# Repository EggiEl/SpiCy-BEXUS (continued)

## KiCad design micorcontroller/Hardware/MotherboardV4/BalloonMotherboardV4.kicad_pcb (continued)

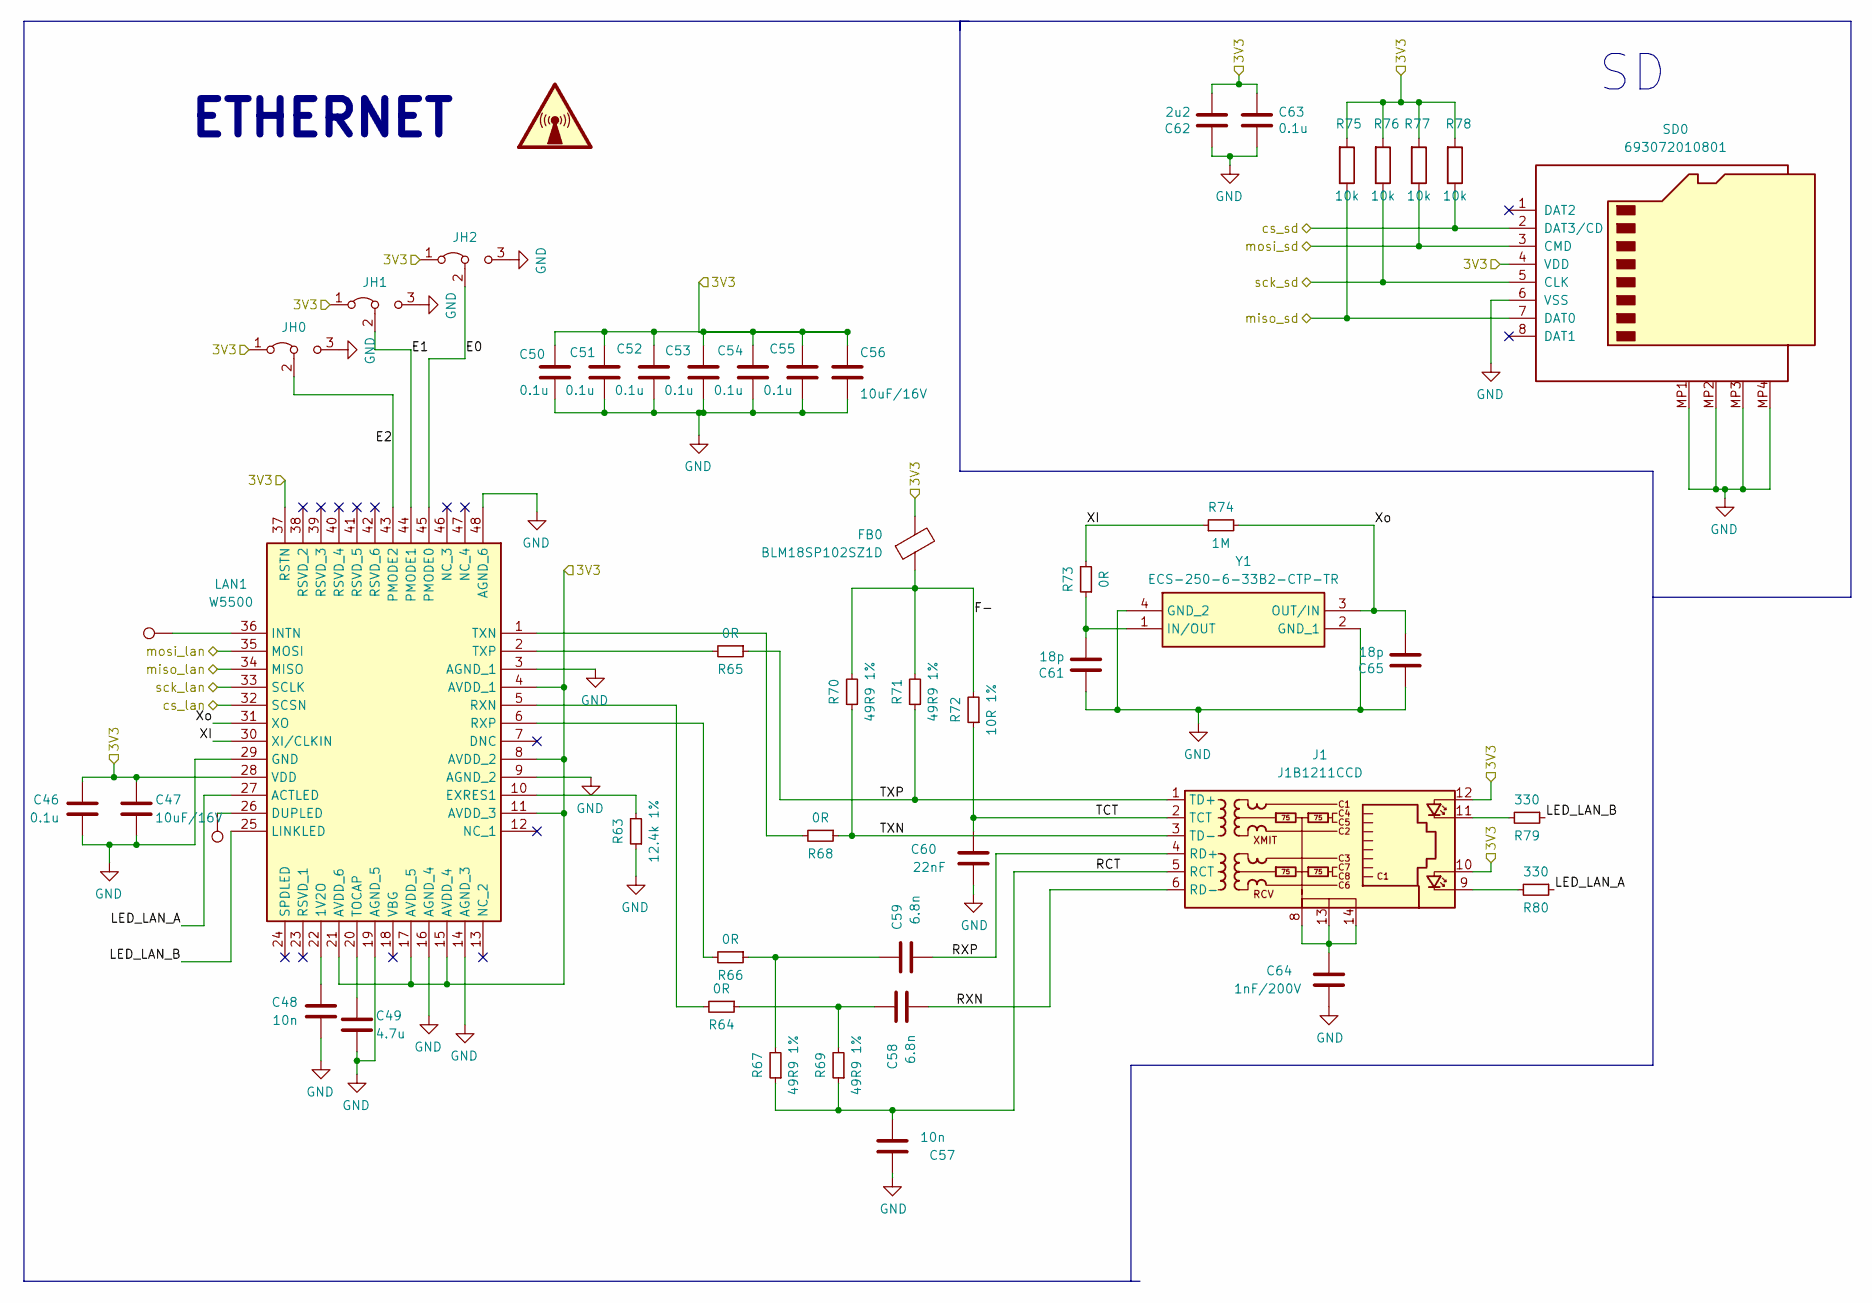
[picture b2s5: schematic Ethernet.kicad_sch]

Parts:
C46, C50, C51, C52, C53, C54, C55, C63: 0.1u; C_0402_1005Metric_Pad0.74x0.62mm_HandSolder
C47, C56: 10uF/16V; C_0805_2012Metric_Pad1.18x1.45mm_HandSolder
C48, C57: 10n; C_0805_2012Metric_Pad1.18x1.45mm_HandSolder
C49: 4.7u; C_0805_2012Metric_Pad1.18x1.45mm_HandSolder
C58, C59: 6.8n; C_0805_2012Metric_Pad1.18x1.45mm_HandSolder
C60: 22nF; C_0805_2012Metric_Pad1.18x1.45mm_HandSolder
C61, C65: 18p; C_0402_1005Metric_Pad0.74x0.62mm_HandSolder
C62: 2u2; C_0805_2012Metric_Pad1.18x1.45mm_HandSolder
C64: 1nF/200V; C_0805_2012Metric_Pad1.18x1.45mm_HandSolder
FB0: BLM18SP102SZ1D; BLM18SP221SN1B; Mouser Part Number 81-BLM18SP102SZ1D
J1: J1B1211CCD; Mouser Part Number 950-J1B1211CCD
JH0, JH1, JH2: Jumper_3_Bridged12; SolderJumper-3_P1.3mm_Bridged12_RoundedPad1.0x1.5mm_NumberL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
LAN1: W5500; QFP50P900X900X160-48N; Mouser Part Number 950-W5500
R63: 12.4k 1%; R_0603_1608Metric_Pad0.98x0.95mm_HandSolder
R64, R65, R66, R68, R73: 0R; R_0603_1608Metric_Pad0.98x0.95mm_HandSolder
R67, R69, R70, R71: 49R9 1%; R_0603_1608Metric_Pad0.98x0.95mm_HandSolder
R72: 10R 1%; R_0603_1608Metric_Pad0.98x0.95mm_HandSolder
R74: 1M; R_0603_1608Metric_Pad0.98x0.95mm_HandSolder
R75, R76, R77, R78: 10k; R_0603_1608Metric_Pad0.98x0.95mm_HandSolder
R79, R80: 330; R_0603_1608Metric_Pad0.98x0.95mm_HandSolder
SD0: 693072010801; Mouser Part Number 710-693072010801
TP3, TP4: TestPoint; TestPoint_Pad_D1.0mm
Y1: ECS-250-6-33B2-CTP-TR; ECS250633B2CTPTR; Mouser Part Number 520-250-6-33B2-CTPTR

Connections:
/3V3lan: C46.2, C47.2, C50.2, C51.2, C52.2, C53.2, C54.2, C55.2, C56.2, C62.2, C63.1, FB0.2, J1.10, J1.12, JH0.1 (A), JH1.1 (A), JH2.1 (A), LAN1.4 (AVDD_1), LAN1.8 (AVDD_2), LAN1.11 (AVDD_3), LAN1.15 (AVDD_4), LAN1.17 (AVDD_5), LAN1.21 (AVDD_6), LAN1.28 (VDD), LAN1.37 (RSTN), R75.2, R76.2, R77.2, R78.2, SD0.4 (VDD); also elsewhere on the board
/EthernetaSD/E0: JH2.2 (C), LAN1.45 (PMODE0)
/EthernetaSD/E1: JH1.2 (C), LAN1.44 (PMODE1)
/EthernetaSD/E2: JH0.2 (C), LAN1.43 (PMODE2)
/EthernetaSD/F-: FB0.1, R70.2, R71.2, R72.2
/EthernetaSD/LED_LAN_A: LAN1.27 (ACTLED), R80.1
/EthernetaSD/LED_LAN_B: LAN1.25 (LINKLED), R79.1
/EthernetaSD/RCT: C57.1, J1.5 (RCT), R67.1, R69.1
/EthernetaSD/RXN: C58.1, J1.6 (RD-)
/EthernetaSD/RXP: C59.1, J1.4 (RD+)
/EthernetaSD/TCT: C60.2, J1.2 (TCT), R72.1
/EthernetaSD/TXN: J1.3 (TD-), R68.1, R70.1
/EthernetaSD/TXP: J1.1 (TD+), R65.1, R71.1
/EthernetaSD/XI: LAN1.30 (XI/CLKIN), R73.2, R74.1
/EthernetaSD/Xo: C65.2, LAN1.31 (XO), R74.2, Y1.3 (OUT/IN)
/EthernetaSD/cs_lan: LAN1.32 (SCSN); also elsewhere on the board
/EthernetaSD/cs_sd: R78.1, SD0.2 (DAT3/CD); also elsewhere on the board
/EthernetaSD/miso_lan: LAN1.34 (MISO); also elsewhere on the board
/EthernetaSD/miso_sd: R75.1, SD0.7 (DAT0); also elsewhere on the board
/EthernetaSD/mosi_lan: LAN1.35 (MOSI); also elsewhere on the board
/EthernetaSD/mosi_sd: R77.1, SD0.3 (CMD); also elsewhere on the board
/EthernetaSD/sck_lan: LAN1.33 (SCLK); also elsewhere on the board
/EthernetaSD/sck_sd: R76.1, SD0.5 (CLK); also elsewhere on the board
GND: C46.1, C47.1, C48.1, C49.1, C50.1, C51.1, C52.1, C53.1, C54.1, C55.1, C56.1, C57.2, C60.1, C61.1, C62.1, C63.2, C64.1, C65.1, JH0.3 (B), JH1.3 (B), JH2.3 (B), LAN1.3 (AGND_1), LAN1.9 (AGND_2), LAN1.14 (AGND_3), LAN1.16 (AGND_4), LAN1.19 (AGND_5), LAN1.29 (GND), LAN1.48 (AGND_6), R63.1, SD0.6 (VSS), SD0.MP1, SD0.MP2, SD0.MP3, SD0.MP4, Y1.2 (GND_1), Y1.4 (GND_2); also elsewhere on the board
unnamed: C58.2, R64.1, R69.2
unnamed: C59.2, R66.1, R67.2
unnamed: C64.2, J1.8, J1.13, J1.14
unnamed: J1.9, R80.2
unnamed: J1.11, R79.2
unnamed: C48.2, LAN1.22 (1V2O)
unnamed: LAN1.26 (DUPLED), TP4.1
unnamed: LAN1.10 (EXRES1), R63.2
unnamed: LAN1.36 (INTN), TP3.1
unnamed: LAN1.5 (RXN), R64.2
unnamed: LAN1.6 (RXP), R66.2
unnamed: C49.2, LAN1.20 (TOCAP)
unnamed: LAN1.1 (TXN), R68.2
unnamed: LAN1.2 (TXP), R65.2
unnamed: C61.2, R73.1, Y1.1 (IN/OUT)

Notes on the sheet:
ETHERNET

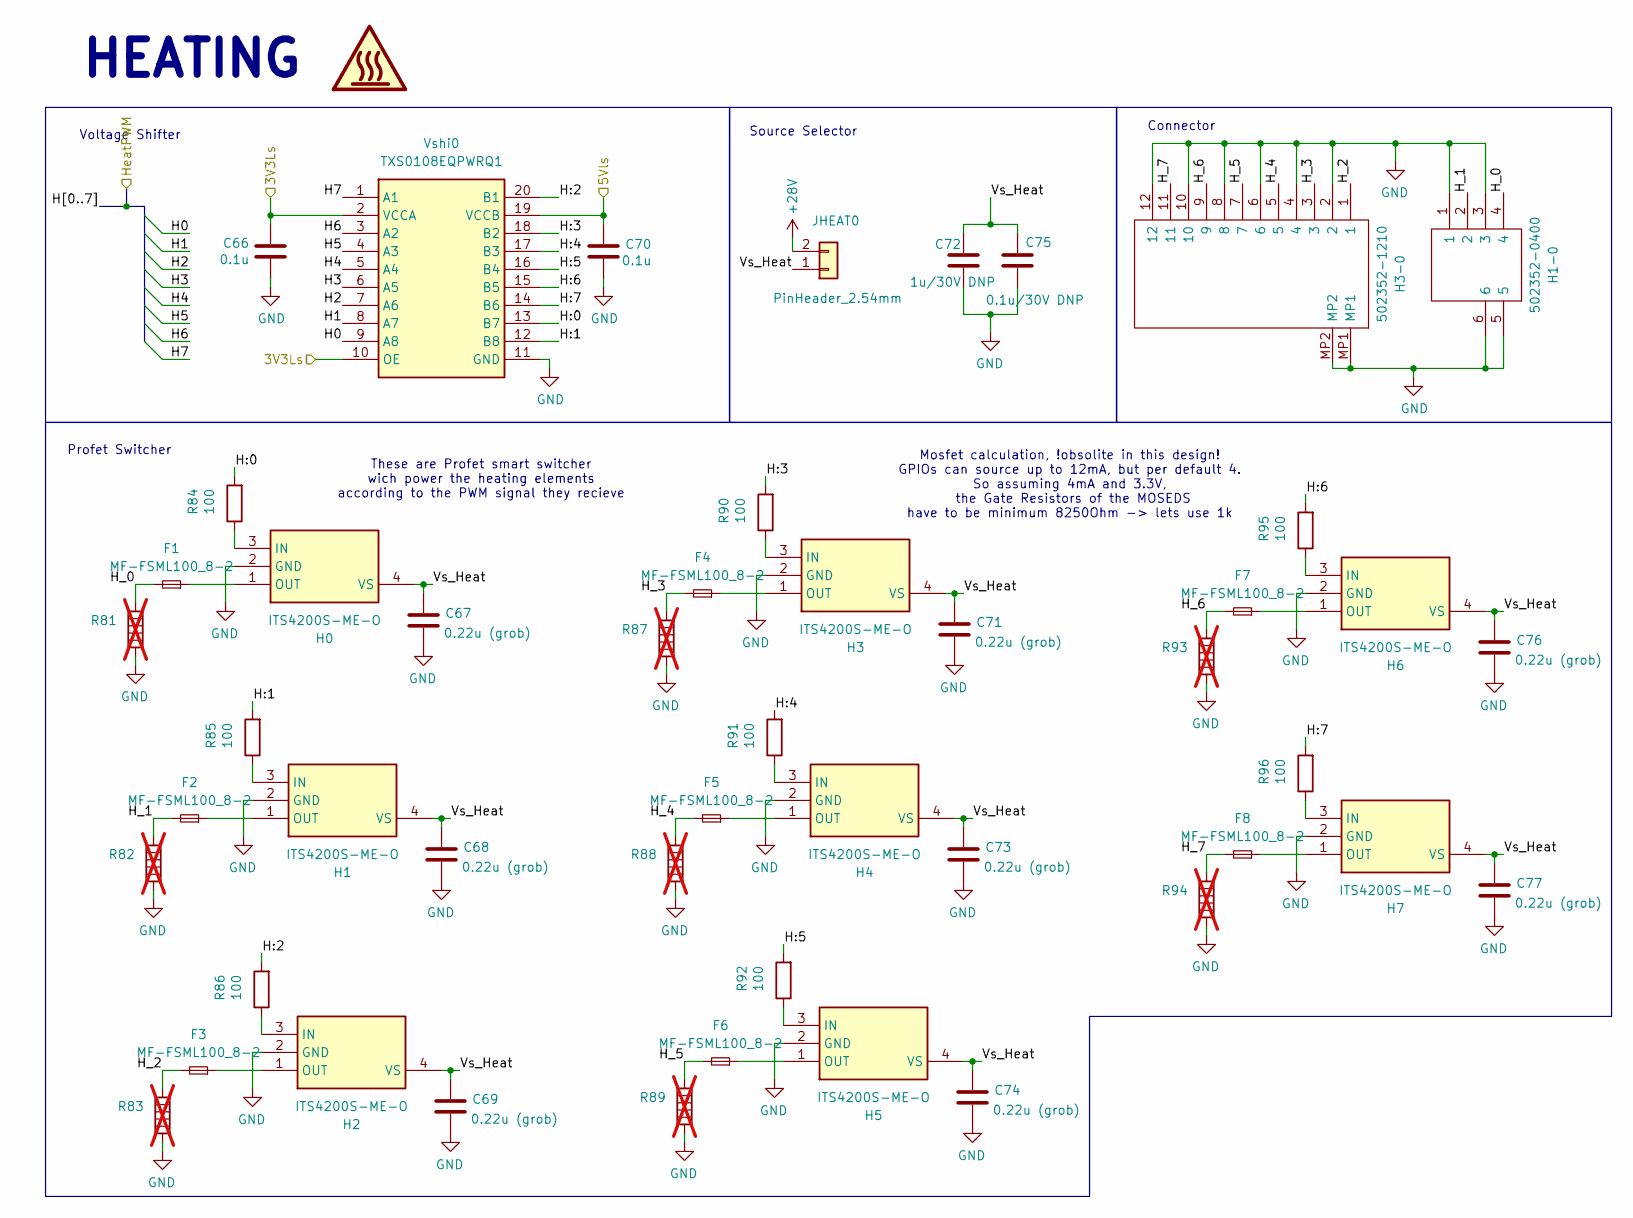
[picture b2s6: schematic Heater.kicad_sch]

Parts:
C66, C70: 0.1u; C_0402_1005Metric
C67, C68, C69, C71, C73, C74, C76, C77: 0.22u (grob); C_0402_1005Metric
C72: 1u/30V DNP; C_0805_2012Metric_Pad1.18x1.45mm_HandSolder
C75: 0.1u/30V DNP; C_0805_2012Metric_Pad1.18x1.45mm_HandSolder
F1, F2, F3, F4, F5, F6, F7, F8: MF-FSML100_8-2; FUSC1608X70N; Mouser Part Number 652-MF-FSML100/8-2
H0, H1, H2, H3, H4, H5, H6, H7: ITS4200S-ME-O; SOT230P700X170-4N; Mouser Part Number 726-ITS4200S-ME-O
H1-0: 502352-0400; 5023520400; Mouser Part Number 538-502352-0400
H3-0: 502352-1210; 5023521210; Mouser Part Number 538-502352-1210
JHEAT0: PinHeader_2.54mm; PinHeader_1x02_P2.54mm_Vertical
R81, R82, R83, R87, R88, R89, R93, R94: Heater; not fitted
R84, R85, R86, R90, R91, R92, R95, R96: 100; R_0603_1608Metric_Pad0.98x0.95mm_HandSolder
Vshi0: TXS0108EQPWRQ1; SOP65P640X120-20N; Mouser Part Number 595-TXS0108EQPWRQ1

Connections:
+28V: JHEAT0.2; also elsewhere on the board
/3V3_rest: C66.1, Vshi0.2 (VCCA), Vshi0.10 (OE); also elsewhere on the board
/5V: C70.1, Vshi0.19 (VCCB); also elsewhere on the board
/Heater/H0: Vshi0.9 (A8); also elsewhere on the board
/Heater/H1: Vshi0.8 (A7); also elsewhere on the board
/Heater/H2: Vshi0.7 (A6); also elsewhere on the board
/Heater/H3: Vshi0.6 (A5); also elsewhere on the board
/Heater/H4: Vshi0.5 (A4); also elsewhere on the board
/Heater/H5: Vshi0.4 (A3); also elsewhere on the board
/Heater/H6: Vshi0.3 (A2); also elsewhere on the board
/Heater/H7: Vshi0.1 (A1); also elsewhere on the board
/Heater/H:0: R84.2, Vshi0.13 (B7)
/Heater/H:1: R85.2, Vshi0.12 (B8)
/Heater/H:2: R86.2, Vshi0.20 (B1)
/Heater/H:3: R90.2, Vshi0.18 (B2)
/Heater/H:4: R91.2, Vshi0.17 (B3)
/Heater/H:5: R92.2, Vshi0.16 (B4)
/Heater/H:6: R95.2, Vshi0.15 (B5)
/Heater/H:7: R96.2, Vshi0.14 (B6)
/Heater/H_0: F1.2, H1-0.4, R81.1
/Heater/H_1: F2.2, H1-0.2, R82.1
/Heater/H_2: F3.2, H3-0.1, R83.1
/Heater/H_3: F4.2, H3-0.3, R87.1
/Heater/H_4: F5.2, H3-0.5, R88.1
/Heater/H_5: F6.2, H3-0.7, R89.1
/Heater/H_6: F7.2, H3-0.9, R93.1
/Heater/H_7: F8.2, H3-0.11, R94.1
/Heater/Vs_Heat: C67.1, C68.1, C69.1, C71.1, C72.2, C73.1, C74.1, C75.1, C76.1, C77.1, H0.4 (VS), H1.4 (VS), H2.4 (VS), H3.4 (VS), H4.4 (VS), H5.4 (VS), H6.4 (VS), H7.4 (VS), JHEAT0.1
GND: C66.2, C67.2, C68.2, C69.2, C70.2, C71.2, C72.1, C73.2, C74.2, C75.2, C76.2, C77.2, H0.2 (GND), H1.2 (GND), H1-0.1, H1-0.3, H1-0.5, H1-0.6, H2.2 (GND), H3.2 (GND), H3-0.2, H3-0.4, H3-0.6, H3-0.8, H3-0.10, H3-0.12, H3-0.MP1, H3-0.MP2, H4.2 (GND), H5.2 (GND), H6.2 (GND), H7.2 (GND), R81.2, R82.2, R83.2, R87.2, R88.2, R89.2, R93.2, R94.2, Vshi0.11 (GND); also elsewhere on the board
unnamed: H0.3 (IN), R84.1
unnamed: F1.1, H0.1 (OUT)
unnamed: H1.3 (IN), R85.1
unnamed: F2.1, H1.1 (OUT)
unnamed: H2.3 (IN), R86.1
unnamed: F3.1, H2.1 (OUT)
unnamed: H3.3 (IN), R90.1
unnamed: F4.1, H3.1 (OUT)
unnamed: H4.3 (IN), R91.1
unnamed: F5.1, H4.1 (OUT)
unnamed: H5.3 (IN), R92.1
unnamed: F6.1, H5.1 (OUT)
unnamed: H6.3 (IN), R95.1
unnamed: F7.1, H6.1 (OUT)
unnamed: H7.3 (IN), R96.1
unnamed: F8.1, H7.1 (OUT)

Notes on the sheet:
Voltage Shifter
Profet Switcher
Source Selector
Mosfet calculation, !obsolite in this design! GPIOs can source up to 12mA, but per default 4. So assuming 4mA and 3.3V, the Gate Resistors of the MOSEDS have to be minimum 8250Ohm -> lets use 1k
These are Profet smart switcher wich power the heating elements according to the PWM signal they recieve
HEATING
Connector

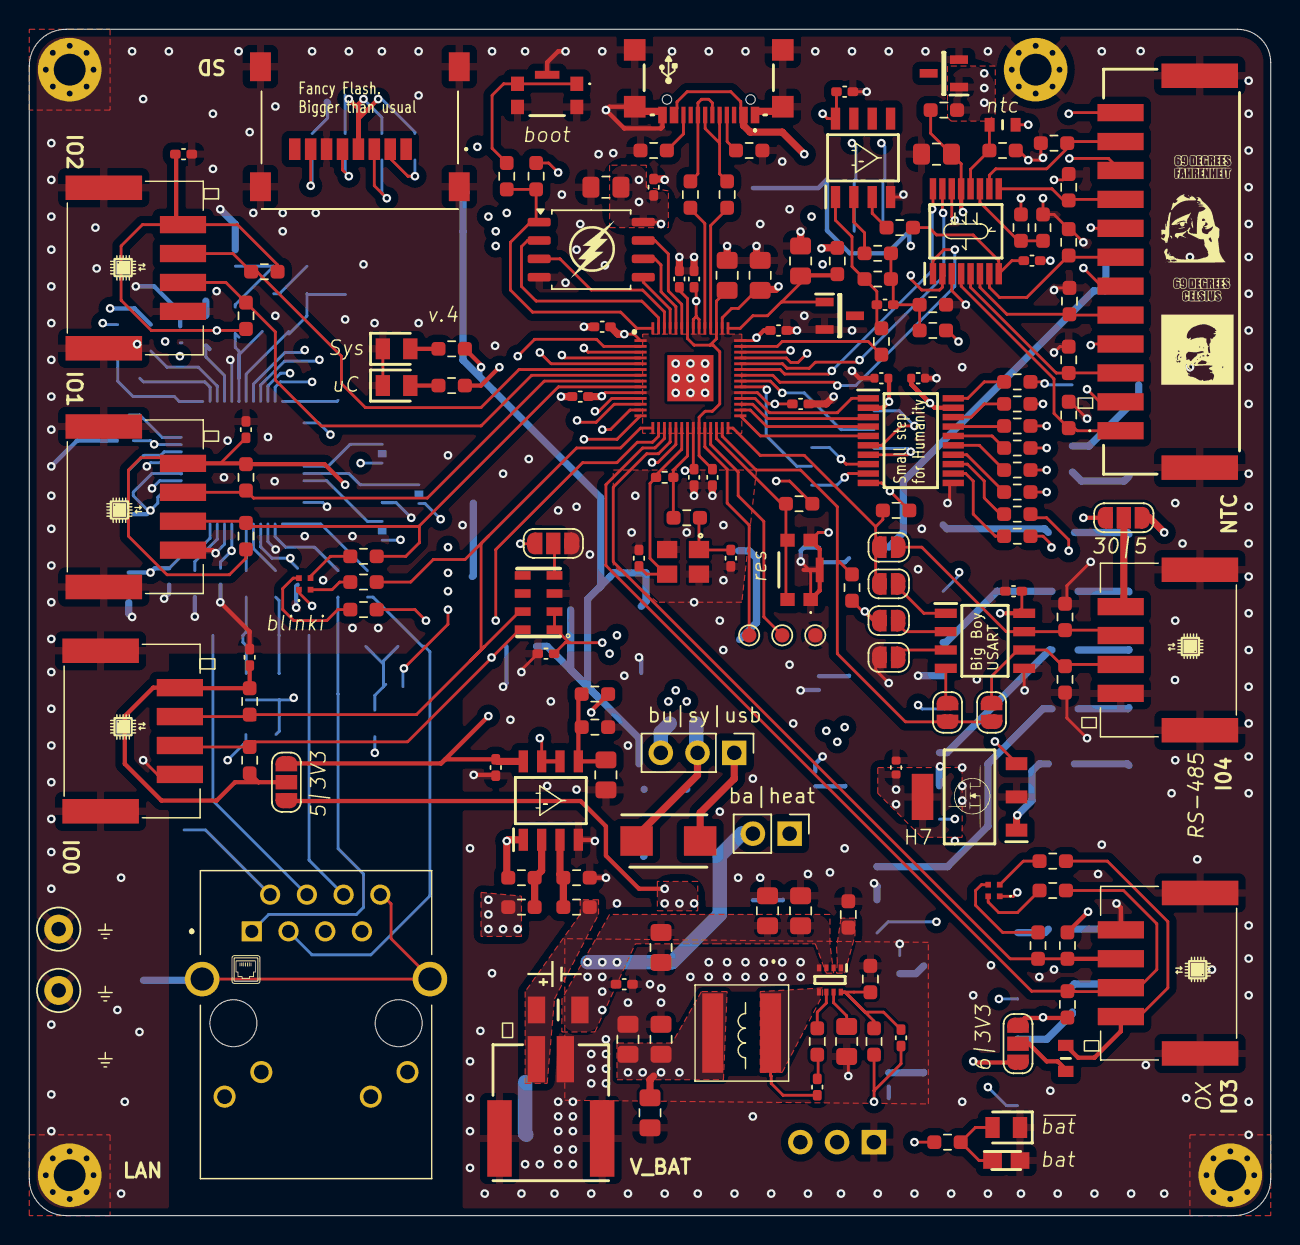
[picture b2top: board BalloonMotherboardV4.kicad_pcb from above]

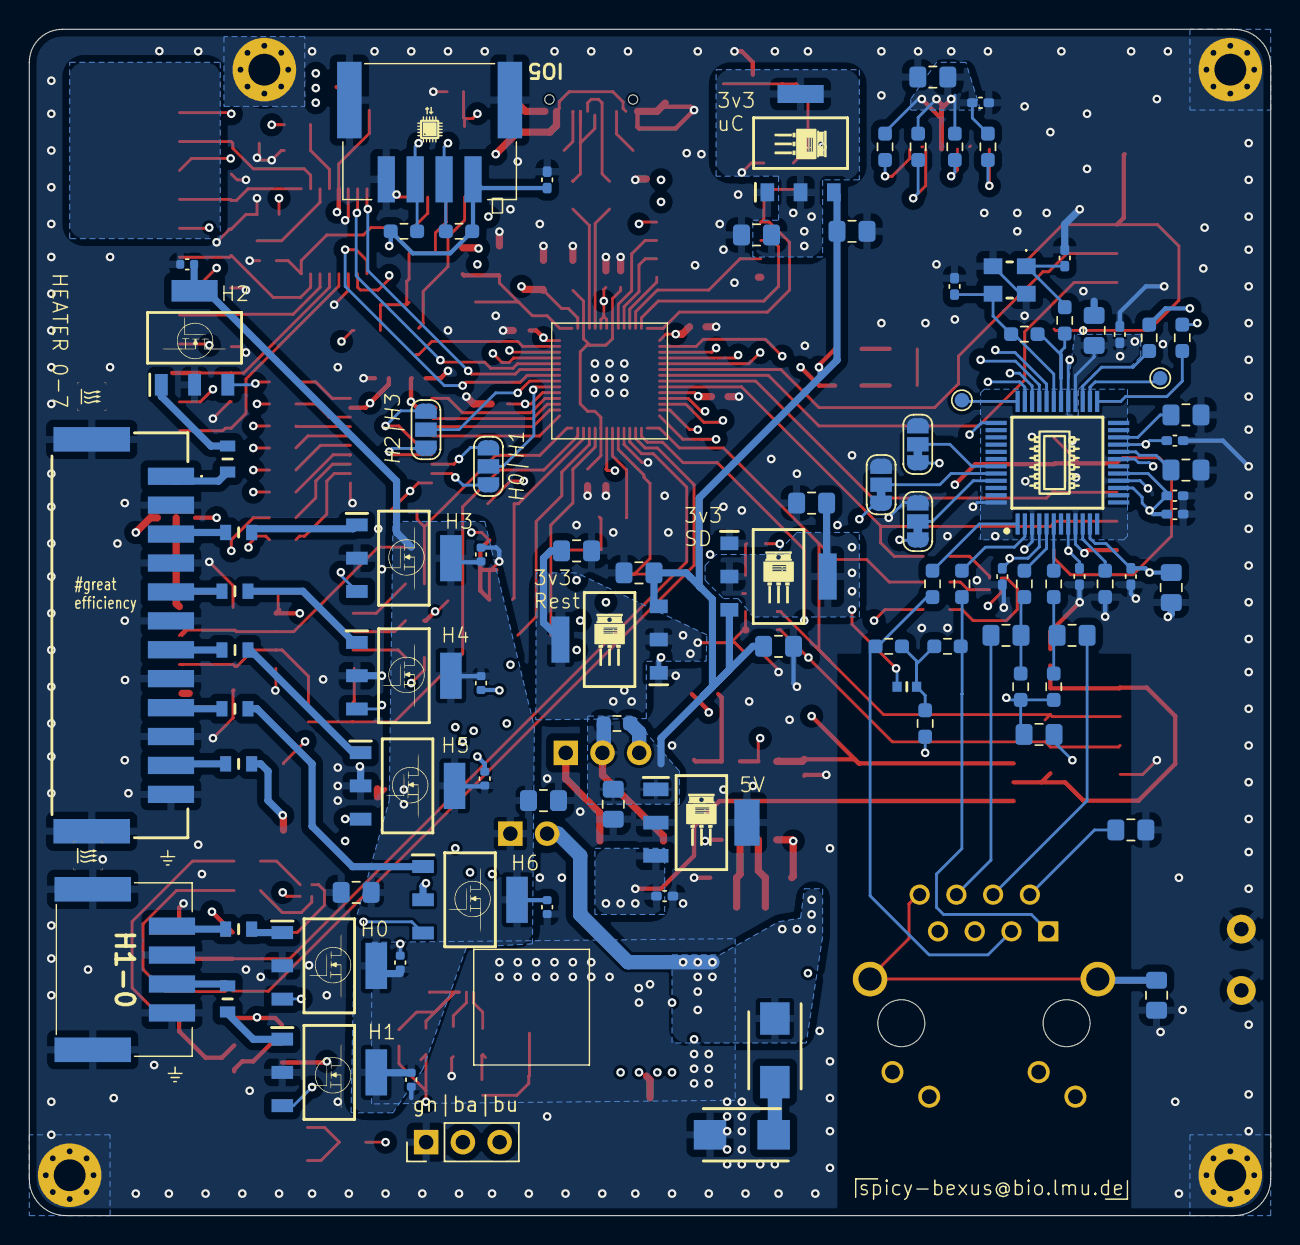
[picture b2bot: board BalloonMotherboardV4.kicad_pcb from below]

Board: 4 copper layers, 85.9 x 82.0 mm, 256 parts (94 on the bottom side), 171 nets.
